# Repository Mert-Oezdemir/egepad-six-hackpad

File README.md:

# EgePad Six Hackpad

Project owner: **Ege Özdemir**

EgePad Six is a compact Hackpad macropad design for the Hack Club Hackpad mission. It uses a 2x3 MX switch matrix, one EC11 rotary encoder, and a Seeed XIAO RP2040 running KMK firmware.

GitHub repository: https://github.com/Mert-Oezdemir/egepad-six-hackpad

This repository follows the Hackpad submission structure described in the official guide: PCB design files, CAD/STEP case files, firmware, and production outputs are kept in separate folders.

Stardance helper: open [START_STARDANCE.html](START_STARDANCE.html) locally for project links and one-click copy fields.

Official reference:
- Hackpad guide: https://hackpad.hackclub.com/guide
- Stardance Hackpad mission guide: https://stardance.hackclub.com/missions/hackpad/guide

## Design Summary

| Item | Value |
| --- | --- |
| Name | EgePad Six |
| Owner | Ege Özdemir |
| MCU | Seeed XIAO RP2040 |
| Inputs | 6 MX switches + 1 EC11 rotary encoder |
| Firmware | KMK / CircuitPython |
| PCB size target | 92mm x 60mm, 2-layer |
| Case size target | 112mm x 80mm x 18mm |
| Switch spacing | 19.05mm center-to-center |
| Mounting | M3 screws + M3 heatset inserts |

## Render / Screenshots

### Macropad Design Render

### Schematic Preview

### PCB Layout Preview

### Case 3D Preview

## Bill Of Materials

| Ref | Component | Qty | Source |
| --- | --- | ---: | --- |
| U1 | Seeed XIAO RP2040 | 1 | Hackpad kit |
| SW1-SW6 | MX-style mechanical switch | 6 | Hackpad kit |
| D1-D6 | 1N4148 through-hole diode | 6 | Hackpad kit |
| ENC1 | EC11 rotary encoder, 20mm D-shaft | 1 | Hackpad kit |
| KC1-KC6 | Blank DSA keycap | 6 | Hackpad kit |
| H1-H6 | M3 x 5 x 4mm heatset insert | 6 | Hackpad kit |
| S1-S6 | M3 x 16mm screw | 6 | Hackpad kit |
| PCB | 2-layer PCB, max 92mm x 60mm | 1 | JLCPCB grant |
| CASE | 3D-printed top and bottom case | 1 set | Printing Legion |

CSV version: [BOM.csv](BOM.csv)

## Wiring Plan

The key matrix uses two rows and three columns:

| Matrix | Column 0 | Column 1 | Column 2 |
| --- | --- | --- | --- |
| Row 0 | SW1 | SW2 | SW3 |
| Row 1 | SW4 | SW5 | SW6 |

XIAO pin plan:

| Function | XIAO Pin |
| --- | --- |
| Row 0 | D0 |
| Row 1 | D1 |
| Col 0 | D2 |
| Col 1 | D3 |
| Col 2 | D4 |
| Encoder A | D8 |
| Encoder B | D9 |
| Encoder button | D10 |

Diode orientation target: `COL2ROW`, with diode stripe toward the row wire.

## Folder Structure

```text
.
├── README.md
├── CAD/
│   ├── assembled-model.STEP
│   ├── Top.STEP
│   ├── Bottom.STEP
│   └── README.md
├── PCB/
│   ├── egepad.kicad_pro
│   ├── egepad.kicad_sch
│   ├── egepad.kicad_pcb
│   └── README.md
├── Firmware/
│   └── main.py
└── production/
    ├── gerbers.zip
    ├── Top.STEP
    ├── Bottom.STEP
    └── main.py
```

## Pre-Submission Status

See [RELEASE_STATUS.md](RELEASE_STATUS.md).

Requirement mapping:

- [Hackpad requirements map](HACKPAD_REQUIREMENTS_MAP.md)
- [Stardance submission handoff](STARDANCE_SUBMISSION.md)
- [Stardance launch helper](START_STARDANCE.html)
- [Mechanical dimensions](CAD/MECHANICAL_DIMENSIONS.md)
- [Firmware notes](Firmware/README.md)

Important note: this environment does not have KiCad CLI or a CAD kernel installed, so the PCB DRC, real Gerber export, and STEP geometry have not been tool-verified here. The repo is prepared as a complete Hackpad submission package scaffold and should be opened in KiCad/Fusion 360 for final manufacturability checks before submitting.

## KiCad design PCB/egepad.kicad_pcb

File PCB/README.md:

# PCB Notes

Owner: Ege Özdemir

Design target:

- Board: 92mm x 60mm, 2 layers.
- MCU: Seeed XIAO RP2040, bottom side, USB-C toward right-side case cutout.
- Matrix: 2 rows x 3 columns, six 1N4148 diodes, COL2ROW.
- Encoder: one EC11 on the right side.

Pin map:

| Net | XIAO pin |
| --- | --- |
| ROW0 | D0 |
| ROW1 | D1 |
| COL0 | D2 |
| COL1 | D3 |
| COL2 | D4 |
| ENCA | D8 |
| ENCB | D9 |
| ENCSW | D10 |

The KiCad files are hand-authored draft files because KiCad CLI is not installed in this environment. Open in KiCad, assign the Hackpad care package XIAO/MX footprints, run ERC/DRC, and export real Gerbers before final submission.

Supporting contract files:

- `pinout.csv`: XIAO pin and firmware signal mapping.
- `matrix-map.csv`: physical key locations, matrix positions, and default keymap.

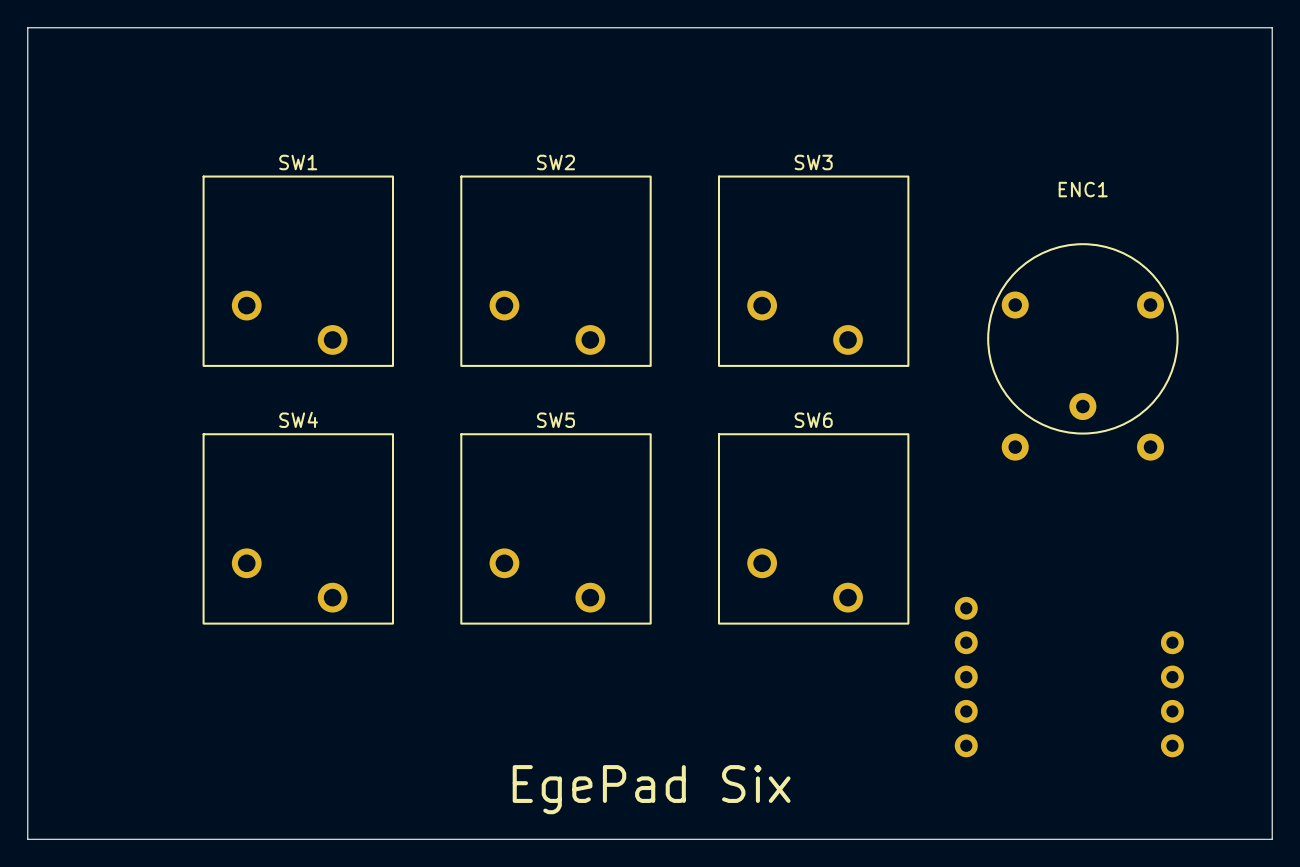
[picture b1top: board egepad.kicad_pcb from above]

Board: 2 copper layers, 92.0 x 60.0 mm, 8 parts (1 on the bottom side), 9 nets, no tracks yet.

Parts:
ENC1: EC11; EC11_DRAFT
SW1, SW2, SW3, SW4, SW5, SW6: MX; MX_1U_DRAFT
U1: XIAO_RP2040; XIAO_RP2040_DRAFT

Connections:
COL0: SW1.1, SW4.1, U1.D2
COL1: SW2.1, SW5.1, U1.D3
COL2: SW3.1, SW6.1, U1.D4
ENCA: ENC1.A, U1.D8
ENCB: ENC1.B, U1.D9
ENCSW: ENC1.SW1, U1.D10
GND: ENC1.C, ENC1.SW2, U1.GND
ROW0: SW1.2, SW2.2, SW3.2, U1.D0
ROW1: SW4.2, SW5.2, SW6.2, U1.D1

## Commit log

2026-06-08 Create EgePad Six hackpad project
2026-06-08 Add GitHub publish helper
2026-06-09 Add source package helper
2026-06-09 Add Stardance submission handoff
2026-06-09 Add Stardance submit helpers
2026-06-09 Map Hackpad requirements to repo evidence
2026-06-09 Add measured CAD and hardware contracts
2026-06-10 Add Stardance launch helper
